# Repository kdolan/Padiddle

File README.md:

Padiddle
========

Padiddle is the name of a game aimed quickly identifying cars with a burnt out headlight by punching the ceiling. The goal of this project is to create an easy to use hardware/software solution that facilitates the playing of padiddle in a vehicle. The design is composed of an Arduino Uno, two piezoelectric sensors to detect when a user punches the ceiling, and a custom PCB that acts as the user interface.

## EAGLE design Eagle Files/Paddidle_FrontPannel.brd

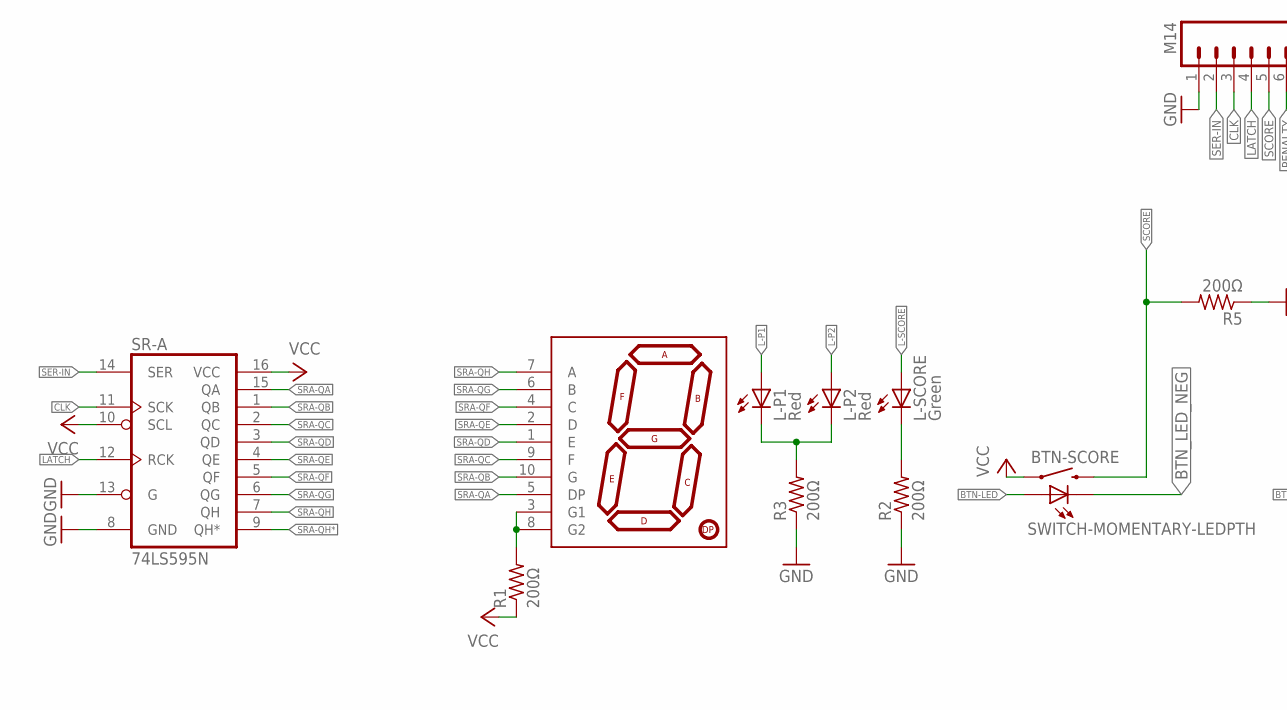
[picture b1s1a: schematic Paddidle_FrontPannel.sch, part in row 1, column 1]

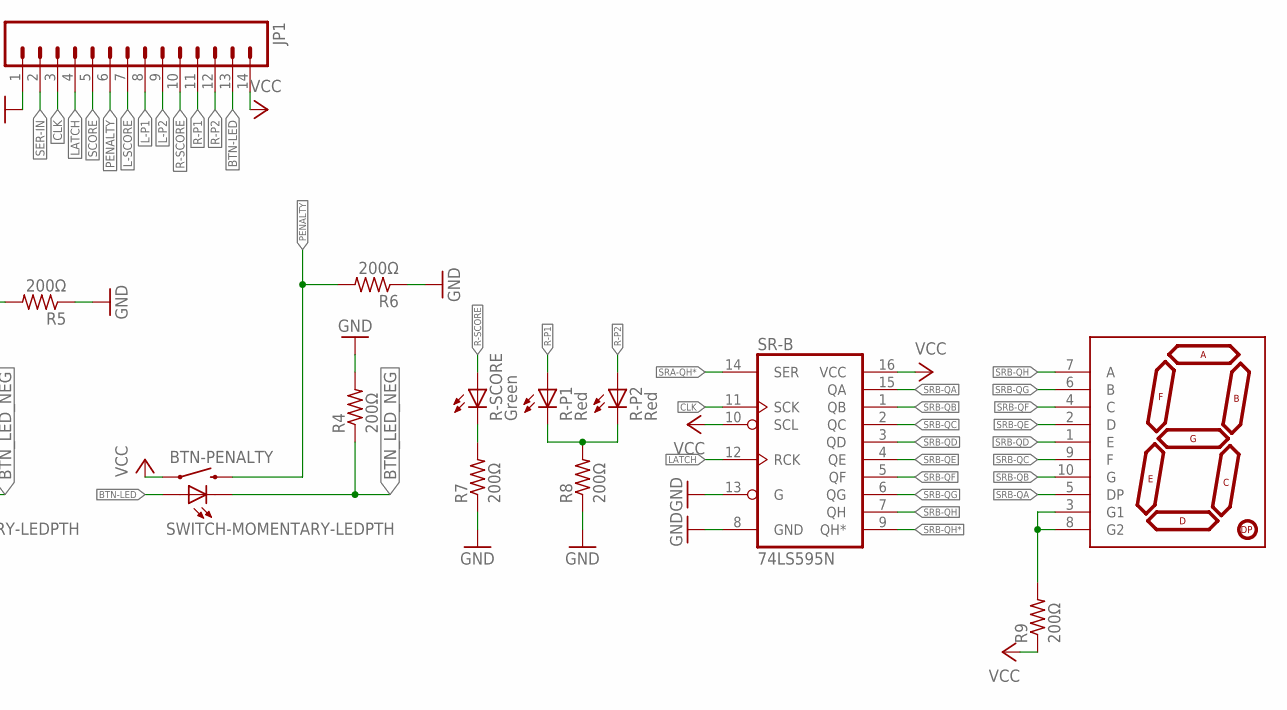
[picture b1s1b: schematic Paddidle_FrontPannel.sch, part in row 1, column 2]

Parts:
7SEG-L, 7SEG-R: 7-SEGMENT-DISPLAY-1"-RED; 7-SEGMENT-1"PTH
BTN-PENALTY: SWITCH-MOMENTARY-LEDPTH; TACTILE-PTH-LED-12MM
BTN-SCORE: SWITCH-MOMENTARY-LEDPTH; TACTILE-PTH-LED-12MM
JP1: M14; 1X14
L-P1, L-P2: Red; LED5MM
L-SCORE: Green; LED5MM
R1, R2, R3, R4, R5, R6, R7, R8, R9: 200Ω; R0805; MPN PFC-W0805LF-03-2000-B
R-P1, R-P2: Red; LED5MM
R-SCORE: Green; LED5MM
SR-A: 74LS595N; DIL16; MPN SN74LS595N
SR-B: 74LS595N; DIL16; MPN SN74LS595N

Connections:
BTN-LED: BTN-PENALTY.A, BTN-SCORE.A, JP1.13
BTN_LED_NEG: BTN-PENALTY.C, BTN-SCORE.C, R4.1
CLK: JP1.3, SR-A.11 (SCK), SR-B.11 (SCK)
GND: JP1.1, R2.1, R3.1, R4.2, R5.1, R6.1, R7.1, R8.1, SR-A.8 (GND), SR-A.13 (G), SR-B.8 (GND), SR-B.13 (G)
L-P1: JP1.8, L-P1.A
L-P2: JP1.9, L-P2.A
L-SCORE: JP1.7, L-SCORE.A
LATCH: JP1.4, SR-A.12 (RCK), SR-B.12 (RCK)
unnamed: L-P1.K (C), L-P2.K (C), R3.2
unnamed: L-SCORE.K (C), R2.2
unnamed: 7SEG-L.3 (G1), 7SEG-L.8 (G2), R1.2
unnamed: R7.2, R-SCORE.K (C)
unnamed: R8.2, R-P1.K (C), R-P2.K (C)
unnamed: 7SEG-R.3 (G1), 7SEG-R.8 (G2), R9.2
PENALTY: BTN-PENALTY.2, JP1.6, R6.2
R-P1: JP1.11, R-P1.A
R-P2: JP1.12, R-P2.A
R-SCORE: JP1.10, R-SCORE.A
SCORE: BTN-SCORE.2, JP1.5, R5.2
SER-IN: JP1.2, SR-A.14 (SER)
SRA-QA: 7SEG-L.5 (DP), SR-A.15 (QA)
SRA-QB: 7SEG-L.10 (G), SR-A.1 (QB)
SRA-QC: 7SEG-L.9 (F), SR-A.2 (QC)
SRA-QD: 7SEG-L.1 (E), SR-A.3 (QD)
SRA-QE: 7SEG-L.2 (D), SR-A.4 (QE)
SRA-QF: 7SEG-L.4 (C), SR-A.5 (QF)
SRA-QG: 7SEG-L.6 (B), SR-A.6 (QG)
SRA-QH: 7SEG-L.7 (A), SR-A.7 (QH)
SRA-QH*: SR-A.9 (QH*), SR-B.14 (SER)
SRB-QA: 7SEG-R.5 (DP), SR-B.15 (QA)
SRB-QB: 7SEG-R.10 (G), SR-B.1 (QB)
SRB-QC: 7SEG-R.9 (F), SR-B.2 (QC)
SRB-QD: 7SEG-R.1 (E), SR-B.3 (QD)
SRB-QE: 7SEG-R.2 (D), SR-B.4 (QE)
SRB-QF: 7SEG-R.4 (C), SR-B.5 (QF)
SRB-QG: 7SEG-R.6 (B), SR-B.6 (QG)
SRB-QH: 7SEG-R.7 (A), SR-B.7 (QH)
SRB-QH*: SR-B.9 (QH*)
VCC: BTN-PENALTY.4 (1), BTN-SCORE.4 (1), JP1.14, R1.1, R9.1, SR-A.10 (SCL), SR-A.16 (VCC), SR-B.10 (SCL), SR-B.16 (VCC)

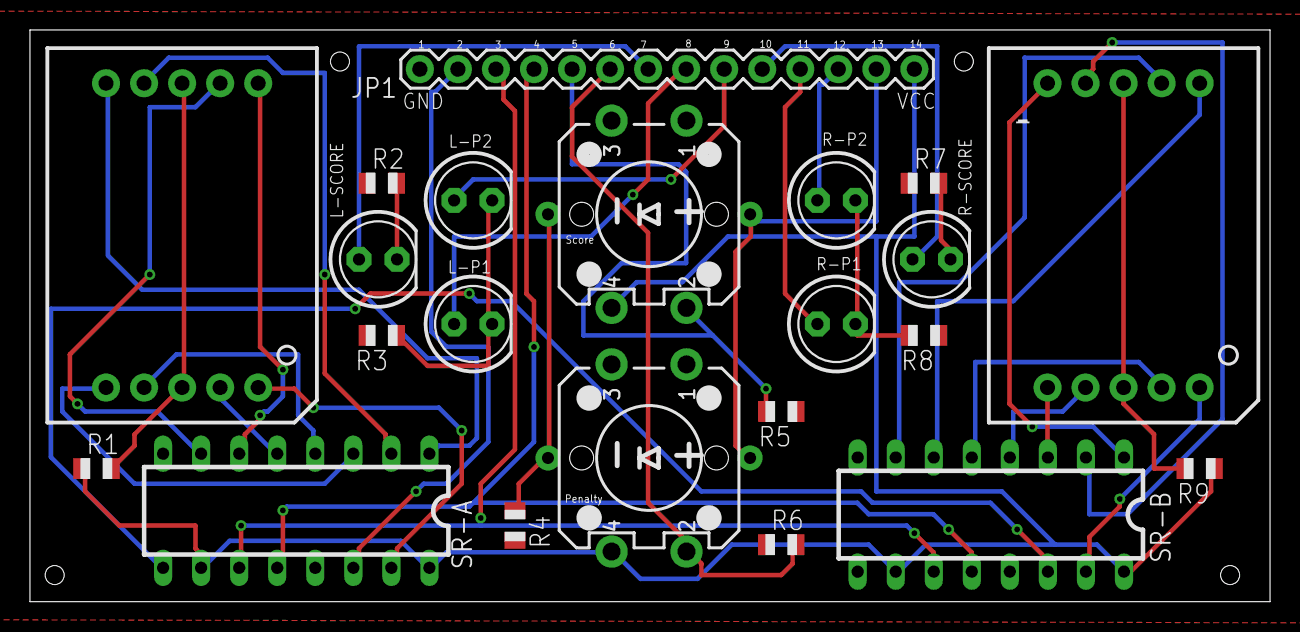
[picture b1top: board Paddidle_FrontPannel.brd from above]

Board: 2 copper layers, 82.8 x 38.2 mm, 22 parts (0 on the bottom side), 38 nets.

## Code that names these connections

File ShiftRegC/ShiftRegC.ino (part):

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    B00000000,  //NULL (Off)
};

int scorePin = 2; //Pin for score button
int penaltyPin = 3; //Pin for penalty button.

int configPin_0 = 4;
int configPin_1 = 5;
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    //digitalWrite(C_latchPin, LOW);
    // shift out the bits:
    //shiftOut(C_dataPin, clockPin, MSBFIRST, C_data);  
    //take the latch pin high so the LEDs will light up:
    //digitalWrite(C_latchPin, HIGH);
    // pause before next value:
    boolean sideDetected;
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

boolean isScore(){
 int score = 0; //O is unset
 while(score==0)
  {
    int scoreState = digitalRead(scorePin);
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  digitalWrite(C_latchPin, LOW);
  // shift out the bits:
  shiftOut(C_dataPin, clockPin, MSBFIRST, C_data);  
  //take the latch pin high so the LEDs will light up:
  digitalWrite(C_latchPin, HIGH);
}

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
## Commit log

2013-11-01 Initial Commit - System working and Installed
    System installed and working in car. Working on bug fixes.
2013-11-03 Code cleanup & Bug Fixes
    -Primary loop is simpler and less verbose.
    -Fixed bug where sensor would trigger many successive penalty or score
    increases while button was pressed. Program now waits until button is
    released to begin checking for input again.
2013-11-04 Adds configuration and competitive game mode
    -Adds configuration with binary switches on pins 4 and 5. Ability to
    change game mode to competitive . Competitive mode allows only one
    person to have a score (ie score cancelation).
    -Misc code improvements
    -Removes zero as a number for numerals constant. Zero is replaced by
    null value (led display off).
2013-11-10 Decrement Score Feature
    Ability to decrement the score of left and right using the penalty and
    score buttons when the score LEDs are not set. Pressing the score button
    decrements left while the penalty button decrements right.
2014-01-27 Redesign and Printed Circuit Board
    This commit includes a complete redesign of the code base as well as
    includes an eagle schematic for a PCB.

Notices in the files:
parts and their libraries:
SparkFun-DigitalIC: Licensing: CC v3.0 Share-Alike You are welcome to use this library for commercial purposes.
